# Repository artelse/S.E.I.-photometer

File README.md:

# S.E.I.-photometer
A lamp replacement board for the vintage S.E.I. photometer.

A replacement light source for the vintage S.E.I. photometer was created by someone with the name Huw[^1]. Here the schematic and board are recreated in Kicad. Datasheets for the components are included as well as any documentation on the S.E.I. photometer that we could find.

For fun, and to stay a bit with the times, I used the *Round Tracks* plugin for the PCB layout. Further, the board has no solder mask or silkscreen, but has full board ENIG gold finish for good connectivity with the battery and enclosure.

I case one needs a board, am happy to send you one at cost. 

[^1]: See Documents folder for details

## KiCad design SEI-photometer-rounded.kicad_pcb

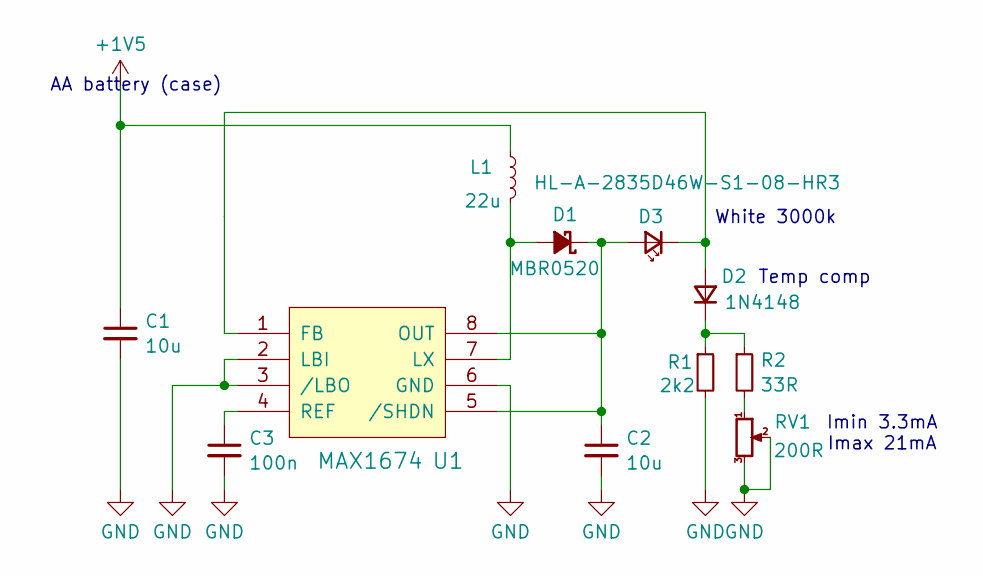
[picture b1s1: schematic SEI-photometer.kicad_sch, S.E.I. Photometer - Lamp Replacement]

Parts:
C1, C2: 10u; C_0805_2012Metric
C3: 100n; C_0603_1608Metric
D1: MBR0520; D_SOD-123
D2: 1N4148; D_SOD-123
D3: HL-A-2835D46W-S1-08-HR3; LED_Everlight-SMD3528_3.5x2.8mm_67-21ST
L1: 22u; L_Coilcraft_LPS5030
R1: 2k2; R_1206_3216Metric
R2: 33R; R_1206_3216Metric
RV1: 200R; Potentiometer_Bourns_PVG3G_Horizontal
U1: MAX1674; 21-0036_U8-1_MXM

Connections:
+1V5: C1.1, L1.1
GND: C1.2, C2.2, C3.2, R1.2, RV1.2, RV1.3, U1.2 (LBI), U1.3 (/LBO), U1.6 (GND)
unnamed: D1.2 (A), L1.2, U1.7 (LX)
unnamed: C2.1, D1.1 (K), D3.2 (A), U1.5 (/SHDN), U1.8 (OUT)
unnamed: D2.2 (A), D3.1 (K), U1.1 (FB)
unnamed: D2.1 (K), R1.1, R2.1
unnamed: R2.2, RV1.1
unnamed: C3.1, U1.4 (REF)

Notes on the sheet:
Imin 3.3mA Imax 21mA
AA battery (case)
Temp comp
White 3000k

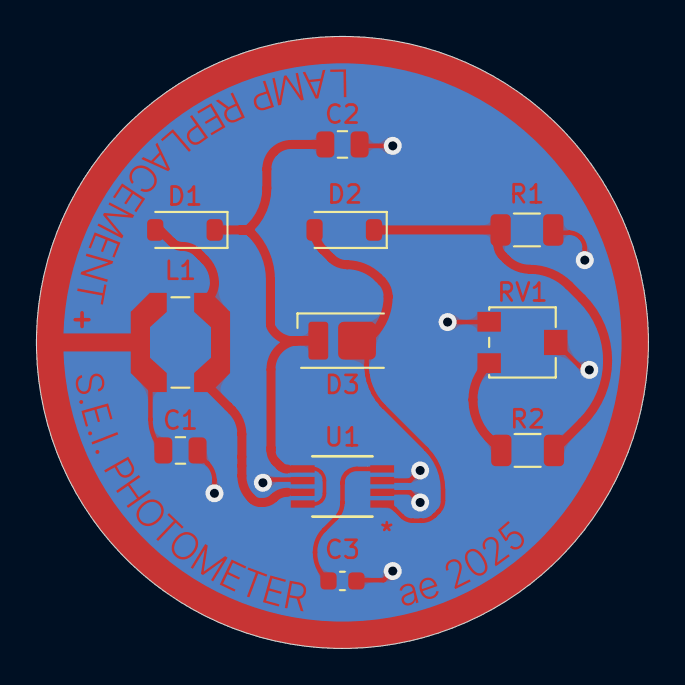
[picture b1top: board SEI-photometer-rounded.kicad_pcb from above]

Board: 2 copper layers, 34.0 x 34.0 mm, 11 parts (0 on the bottom side), 8 nets.

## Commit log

2025-08-04 Added project files.
2025-08-04 Created a folder.
2025-08-04 Deleted S.E.I. schematic.pdf
2025-08-04 Rename S.E.I.photometer.pdf to Documents/S.E.I.photometer.pdf
2025-08-04 Rename S.E.I.repair manual.pdf to Documents/S.E.I.repair manual.pdf
2025-08-04 Rename SEI-photometer.pdf to SEI-photometer-schematic.pdf
2025-08-04 Rename Picker,Fred_Taming-the-S.E.I.-meter.pdf to Documents/Picker,Fred_Taming-the-S.E.I.-meter.pdf
2025-08-04 Rename pvg3.pdf to Datasheets/pvg3.pdf
2025-08-04 Rename 2410121258_HONGLITRONIC-Hongli-Zhihui--HONGLITRONIC-HL-A-3528H343W-S1-13HL-HR3-SDCM-6-2800K-3100K_C516145.pdf to Datasheets/2410121258_HONGLITRONIC-Hongli-Zhihui--HONGLITRONIC-HL-A-3528H343W-S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
2025-08-04 Rename 1N4148W_C2099.pdf to Datasheets/1N4148W_C2099.pdf
2025-08-04 Rename MAX1674-MAX1676.pdf to Datasheets/MAX1674-MAX1676.pdf
2025-08-04 Rename MBR0540T1-D.PDF to Datasheets/MBR0540T1-D.PDF
2025-08-04 Rename SEI LED replacement light source.pdf to Documents/SEI LED replacement light source.pdf
